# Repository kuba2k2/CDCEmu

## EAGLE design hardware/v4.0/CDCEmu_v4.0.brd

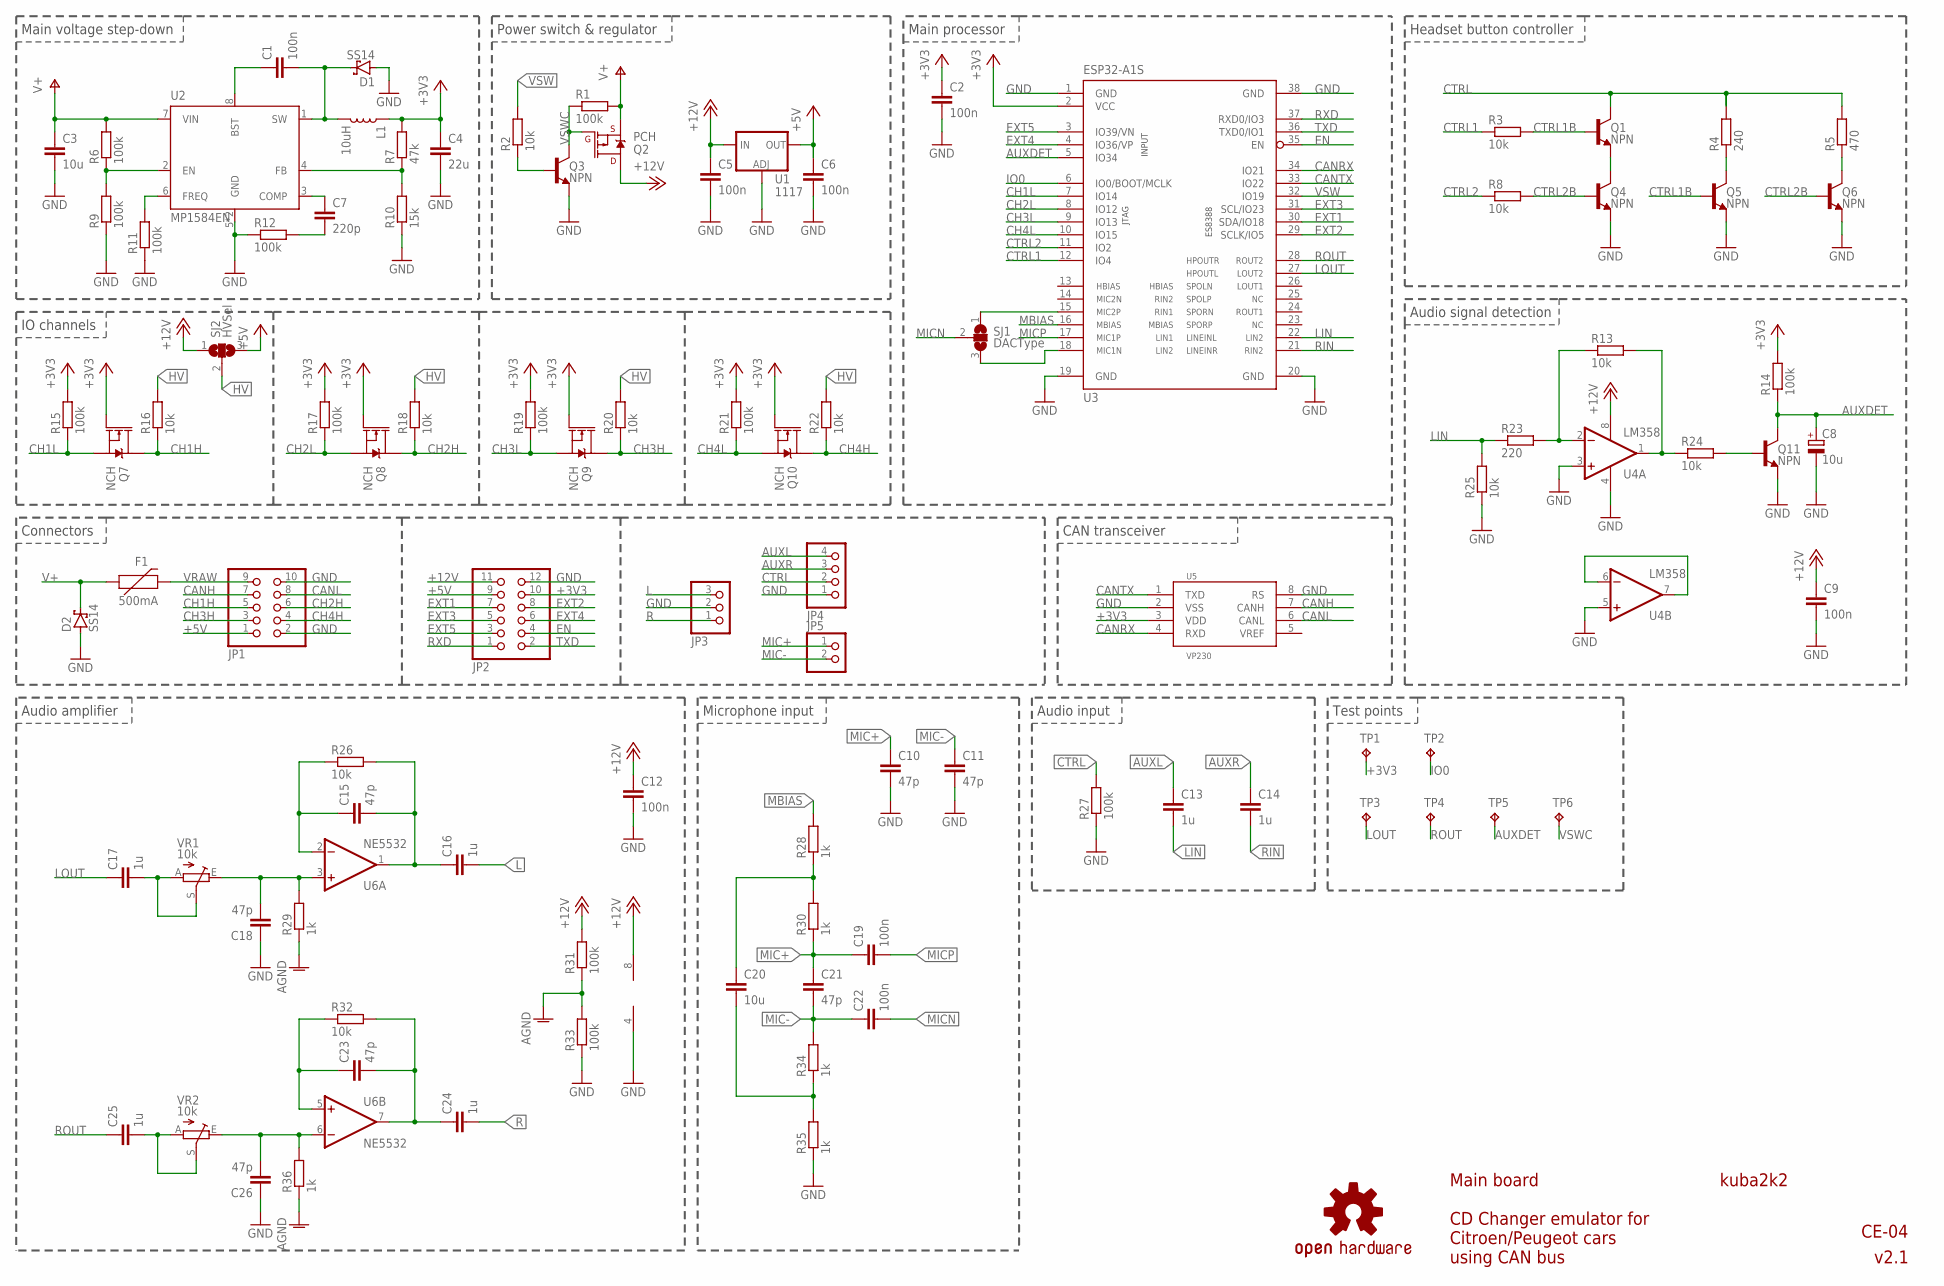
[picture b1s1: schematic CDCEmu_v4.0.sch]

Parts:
C1, C2, C5, C6, C9, C12, C19, C22: 100n; C0805
C3, C20: 10u; C1206
C4: 22u; C1206
C7: 220p; C0805
C8: 10u; C1206-POL
C10, C11, C15, C18, C21, C23, C26: 47p; C0805
C13, C14, C16, C17, C24, C25: 1u; C0805
D1, D2: SS14; DO-214AC
F1: 500mA; 0805
JP1: PINHD-2X5/90; 2X05/90
JP2: PINHD-2X6/90; 2X06/90
JP3: PINHD-1X3/90; 1X03/90
JP4: PINHD-1X4/90; 1X04/90
JP5: PINHD-1X2/90; 1X02/90
L1: 10uH; CR75
Q1, Q3, Q4, Q5, Q6, Q11: NPN; SOT23-3
Q2: PCH; SOT23-3
Q7, Q8, Q9, Q10: NCH; SOT23-3
R1, R6, R9, R11, R12, R14, R15, R17, R19, R21, R27, R31, R33: 100k; R0805
R2, R3, R8, R13, R16, R18, R20, R22, R24, R25, R26, R32: 10k; R0805
R4: 240; R0805
R5: 470; R0805
R7: 47k; R0805
R10: 15k; R0805
R23: 220; R0805
R28, R29, R30, R34, R35, R36: 1k; R0805
SJ1: DACType; SJ_2
SJ2: HVSel; SJ_2
TP1, TP2, TP3, TP4, TP5, TP6: TPB1,27; B1,27
U1: 1117; SOT223
U2: MP1584EN; SO08-PAD
U3: ESP32-A1S
U4: LM358; SO08
U5: VP230; SO08
U6: NE5532; SO08
U$1: OSHW-LOGO; OSHWLOGO_TOP_0.2_OUTLINE
VR1, VR2: 10k; CA6V

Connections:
+3V3: C2.1, C4.1, JP2.10, L1.P$1 (1), Q7.1 (G), Q8.1 (G), Q9.1 (G), Q10.1 (G), R7.2, R14.2, R15.2, R17.2, R19.2, R21.2, TP1.TP, U3.2 (VCC), U5.3 (VDD)
+5V: C6.1, JP1.1, JP2.9, SJ2.3, U1.2 (OUT), U1.4 (OUT)
+12V: C5.1, C9.1, C12.1, JP2.11, Q2.3 (D), R31.2, SJ2.1, U1.3 (IN), U4.8 (V+), U6.8 (V+)
AGND: R29.1, R31.1, R33.2, R36.1
AUXDET: C8.1 (+), Q11.3 (C), R14.1, TP5.TP, U3.5 (IO34)
AUXL: C13.1, JP4.4
AUXR: C14.1, JP4.3
BST: C1.1, U2.8 (BST)
CANH: JP1.7, U5.7 (CANH)
CANL: JP1.8, U5.6 (CANL)
CANRX: U3.34 (IO21), U5.4 (RXD)
CANTX: U3.33 (IO22), U5.1 (TXD)
CCE: Q1.2 (E), Q4.3 (C)
CH1H: JP1.5, Q7.3 (D), R16.1
CH1L: Q7.2 (S), R15.1, U3.7 (IO14)
CH2H: JP1.6, Q8.3 (D), R18.1
CH2L: Q8.2 (S), R17.1, U3.8 (IO12)
CH3H: JP1.3, Q9.3 (D), R20.1
CH3L: Q9.2 (S), R19.1, U3.9 (IO13)
CH4H: JP1.4, Q10.3 (D), R22.1
CH4L: Q10.2 (S), R21.1, U3.10 (IO15)
COMP: C7.1, U2.3 (COMP)
COMPD: C7.2, R12.2
CTRL: JP4.2, Q1.3 (C), R4.2, R5.2, R27.2
CTRL1: R3.1, U3.12 (IO4)
CTRL1B: Q1.1 (B), Q5.1 (B), R3.2
CTRL2: R8.1, U3.11 (IO2)
CTRL2B: Q4.1 (B), Q6.1 (B), R8.2
DET-: R13.1, R23.2, U4.2 (-IN)
DETOUT: R13.2, R24.1, U4.1 (OUT)
DET_B: Q11.1 (B), R24.2
EN: JP2.4, U3.35 (EN)
EXT1: JP2.7, U3.30 (SDA/IO18)
EXT2: JP2.8, U3.29 (SCLK/IO5)
EXT3: JP2.5, U3.31 (SCL/IO23)
EXT4: JP2.6, U3.4 (IO36/VP)
EXT5: JP2.3, U3.3 (IO39/VN)
FB: R7.1, R10.2, U2.4 (FB)
FREQ: R11.2, U2.6 (FREQ)
GND: C2.2, C3.2, C4.2, C5.2, C6.2, C8.2 (-), C9.2, C10.2, C11.2, C12.2, C18.1, C26.1, D1.A, D2.A, JP1.2, JP1.10, JP2.12, JP3.2, JP4.1, Q3.2 (E), Q4.2 (E), Q5.2 (E), Q6.2 (E), Q11.2 (E), R9.1, R10.1, R11.1, R12.1, R25.1, R27.1, R33.1, R35.1, U1.1 (ADJ), U2.5 (GND), U2.PAD (GND), U3.1 (GND), U3.19 (GND), U3.20 (GND), U3.38 (GND), U4.3 (+IN), U4.4 (V-), U4.5 (+IN), U5.2 (VSS), U5.8 (RS), U6.4 (V-)
HV: R16.2, R18.2, R20.2, R22.2, SJ2.2
IO0: TP2.TP, U3.6 (IO0/BOOT/MCLK)
L: C16.2, JP3.3
LF: C17.2, VR1.A, VR1.S
LFB: C15.2, C16.1, R26.2, U6.1 (OUT)
LIN: C13.2, R23.1, R25.2, U3.22 (LINEINL/LIN2)
LNEG: C15.1, R26.1, U6.2 (-IN)
LOUT: C17.1, TP3.TP, U3.27 (HPOUTL/LOUT2)
LPOS: C18.2, R29.2, U6.3 (+IN), VR1.E
MBIAS: R28.2, U3.16 (MBIAS)
MG+: C20.1, R28.1, R30.2
MG-: C20.2, R34.1, R35.2
MIC1N: SJ1.3, U3.18 (MIC1N/LIN2)
MIC+: C10.1, C19.1, C21.1, JP5.1, R30.1
MIC-: C11.1, C21.2, C22.1, JP5.2, R34.2
MICN: C22.2, SJ1.2
MICP: C19.2, U3.17 (MIC1P/LIN1)
MPEN: R6.1, R9.2, U2.2 (EN)
Q8C: Q5.3 (C), R4.1
Q9C: Q6.3 (C), R5.1
R: C24.2, JP3.1
RF: C25.2, VR2.A, VR2.S
RFB: C23.2, C24.1, R32.2, U6.7 (OUT)
RIN: C14.2, U3.21 (LINEINR/RIN2)
RIN1: SJ1.1, U3.15 (MIC2P/RIN1)
RNEG: C23.1, R32.1, U6.5 (+IN)
ROUT: C25.1, TP4.TP, U3.28 (HPOUTR/ROUT2)
RPOS: C26.2, R36.2, U6.6 (-IN), VR2.E
RXD: JP2.1, U3.37 (RXD0/IO3)
SW: C1.2, D1.C, L1.P$2 (2), U2.1 (SW)
TXD: JP2.2, U3.36 (TXD0/IO1)
U4FB: U4.6 (-IN), U4.7 (OUT)
V+: C3.1, D2.C, F1.1, Q2.2 (S), R1.2, R6.2, U2.7 (VIN)
VRAW: F1.2, JP1.9
VSW: R2.2, U3.32 (IO19)
VSWB: Q3.1 (B), R2.1
VSWC: Q2.1 (G), Q3.3 (C), R1.1, TP6.TP

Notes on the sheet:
Audio amplifier
Power switch & regulator
Headset button controller
Microphone input
kuba2k2
v2.1
CE-04
CD Changer emulator for Citroen/Peugeot cars using CAN bus
Main board
Audio signal detection
IO channels
Main voltage step-down
Main processor
Connectors
CAN transceiver
Audio input
Test points

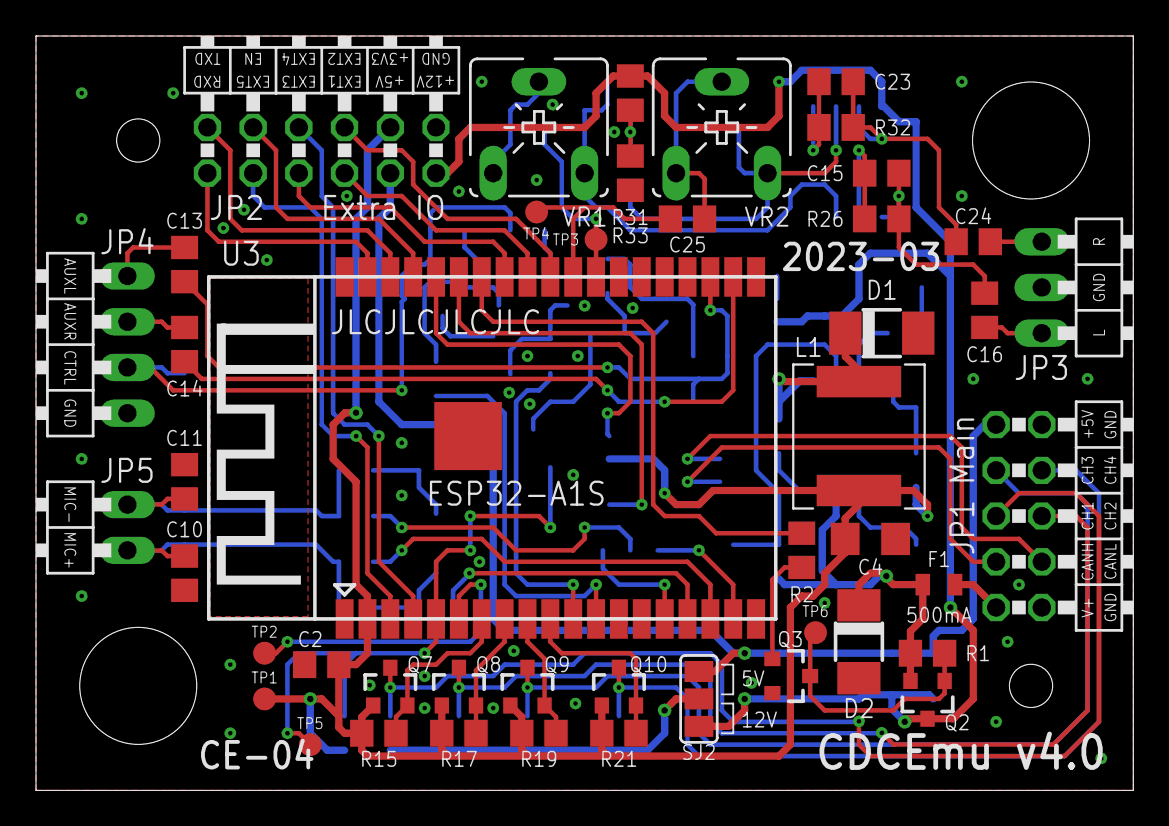
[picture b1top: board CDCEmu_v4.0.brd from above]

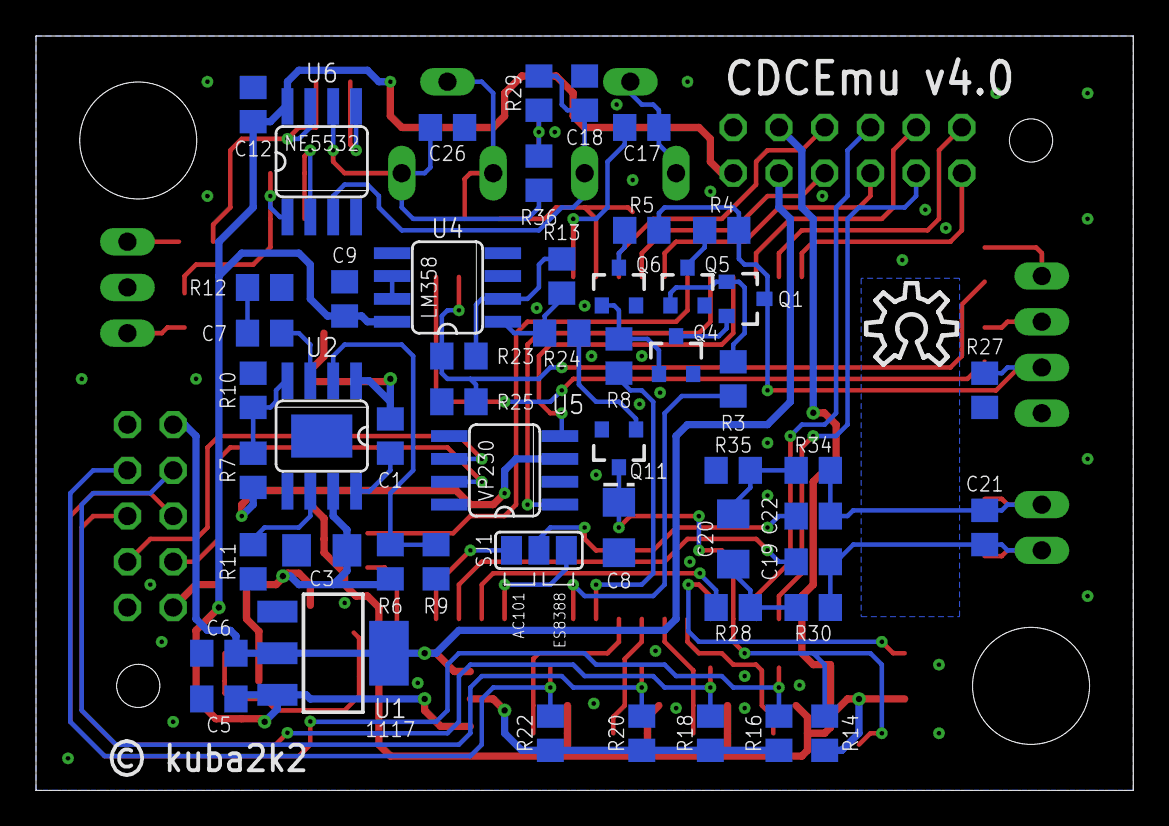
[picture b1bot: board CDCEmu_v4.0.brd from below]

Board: 2 copper layers, 61.0 x 41.9 mm, 99 parts (53 on the bottom side), 77 nets.

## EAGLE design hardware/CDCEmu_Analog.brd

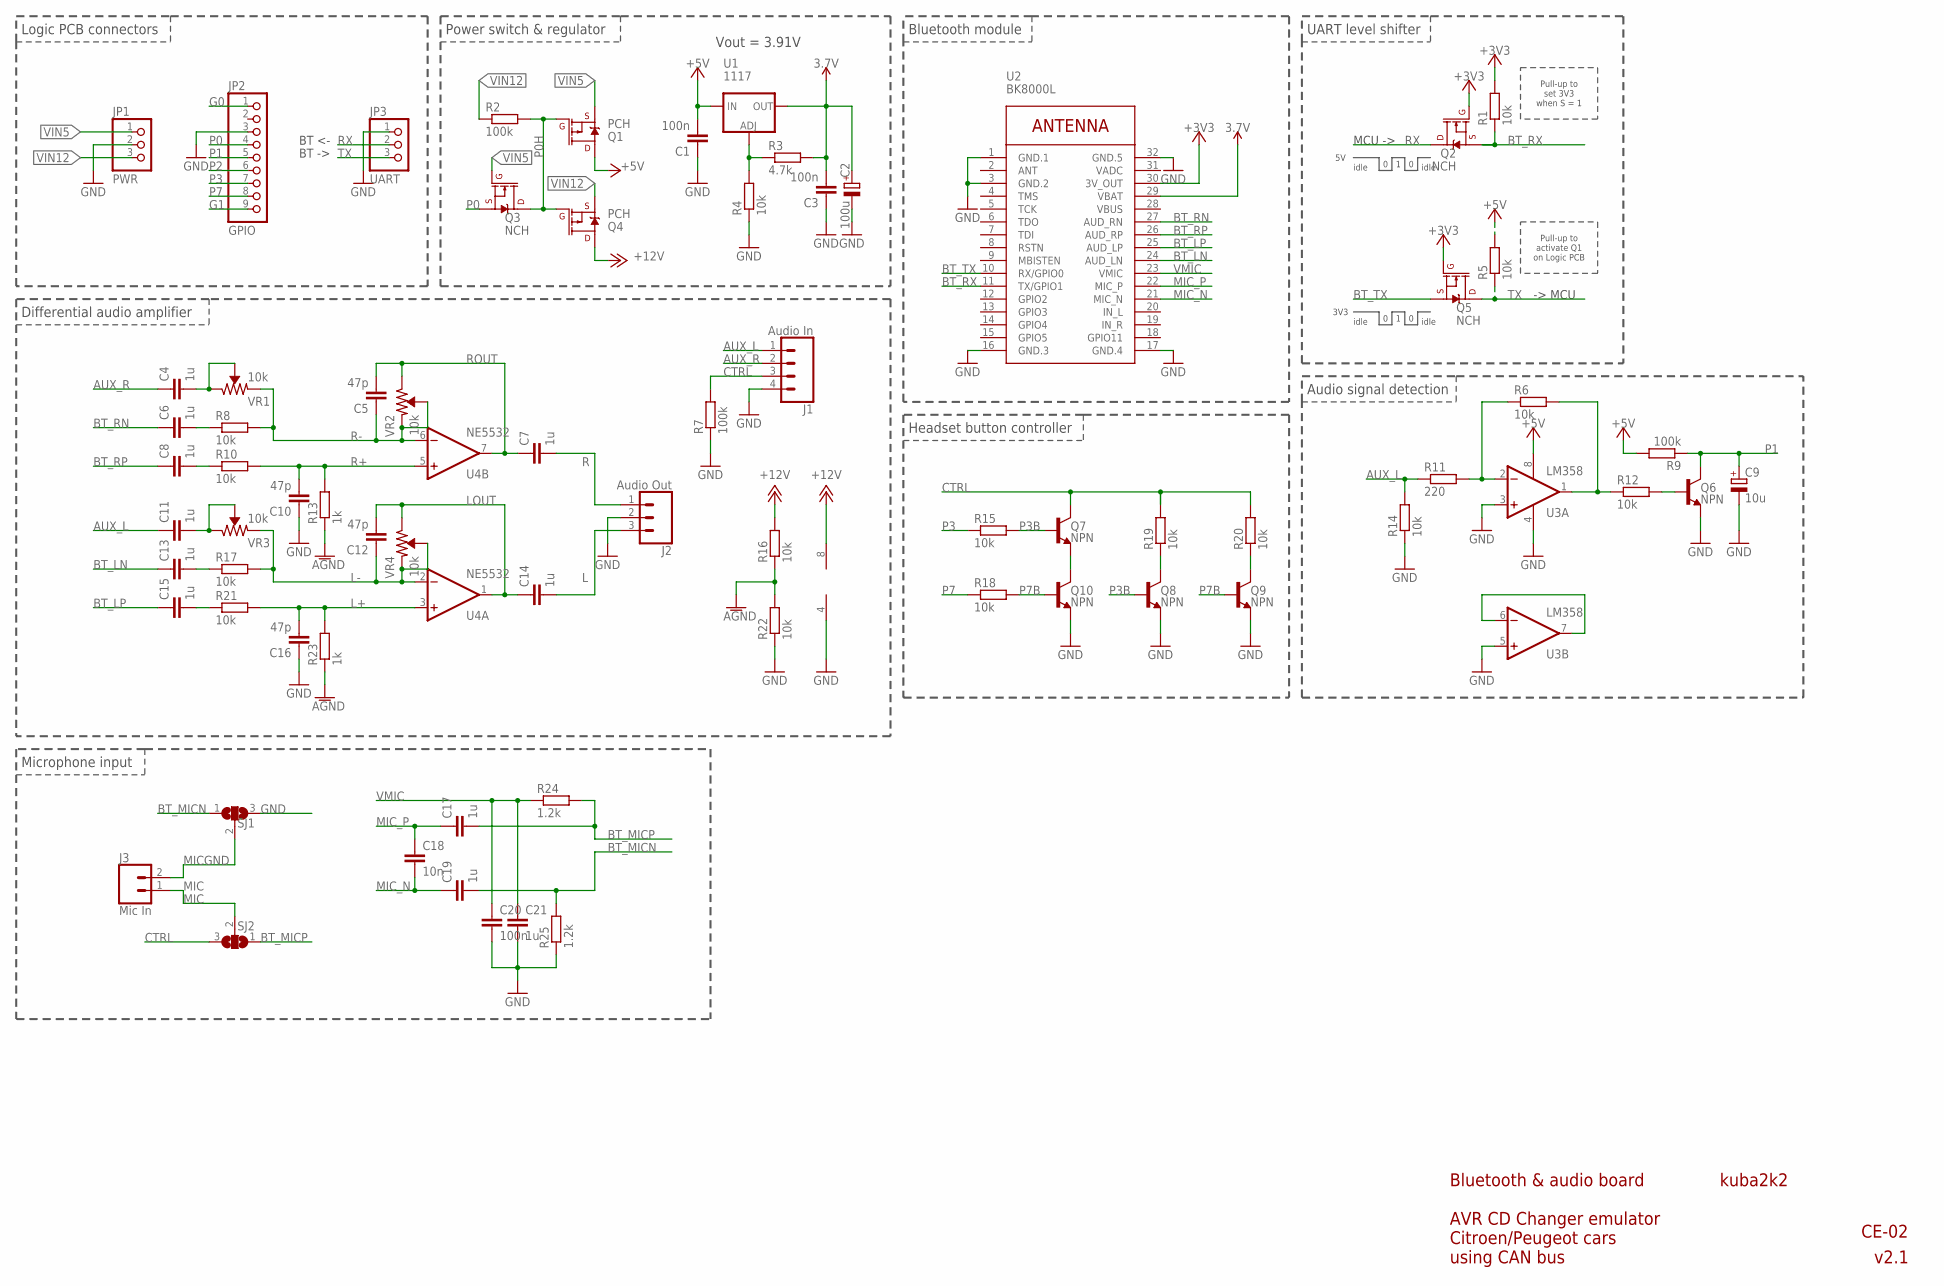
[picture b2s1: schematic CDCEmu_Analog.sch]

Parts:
C1, C3, C20: 100n; C0805
C2: 100u; SMC_B
C4, C6, C7, C8, C11, C13, C14, C15, C17, C19, C21: 1u; C0805
C5, C10, C12, C16: 47p; C0805
C9: 10u; C1206-POL
C18: 10n; C0805
J1: Audio In; JST-4-PTH
J2: Audio Out; JST-3-PTH
J3: Mic In; JST-2-PTH
JP1: PWR; 1X03
JP2: GPIO; 1X09
JP3: UART; 1X03
Q1, Q4: PCH; SOT23-3
Q2, Q3, Q5: NCH; SOT23-3
Q6, Q7, Q8, Q9, Q10: NPN; SOT23-3
R1, R4, R5, R6, R8, R10, R12, R14, R15, R16, R17, R18, R19, R20, R21, R22: 10k; R0805
R2, R7, R9: 100k; R0805
R3: 4.7k; R0805
R11: 220; R0805
R13, R23: 1k; R0805
R24, R25: 1.2k; R0805
SJ1, SJ2: SJ2W; SJ_2
U1: 1117; SOT223
U2: BK8000L; WIRELESS-BLUETOOTH-BK8000
U3: LM358; SO08
U4: NE5532; SO08
VR1, VR2, VR3, VR4: 10k; TRIMPOT-SMD-TC33X

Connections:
3.7V: C2.+, C3.2, R3.2, U1.2 (OUT), U1.4 (OUT), U2.29 (VBAT)
+3V3: Q2.1 (G), Q5.1 (G), R1.2, U2.30 (3V_OUT)
+5V: C1.2, Q1.3 (D), R5.2, R9.2, U1.3 (IN), U3.8 (V+)
+12V: Q4.3 (D), R16.2, U4.8 (V+)
ADJ: R3.1, R4.2, U1.1 (ADJ)
AGND: R13.1, R16.1, R22.2, R23.1
AUX_L: C11.1, J1.1, R11.1, R14.2
AUX_R: C4.1, J1.2
BT_LN: C13.1, U2.24 (AUD_LN)
BT_LP: C15.1, U2.25 (AUD_LP)
BT_MICN: C19.2, R25.2, SJ1.1
BT_MICP: C17.2, R24.2, SJ2.1
BT_RN: C6.1, U2.27 (AUD_RN)
BT_RP: C8.1, U2.26 (AUD_RP)
BT_RX: Q2.2 (S), R1.1, U2.11 (TX/GPIO1)
BT_TX: Q5.2 (S), U2.10 (RX/GPIO0)
CCE: Q7.2 (E), Q10.3 (C)
CTRL: J1.3, Q7.3 (C), R7.2, R19.2, R20.2, SJ2.3
DET-: R6.1, R11.2, U3.2 (-IN)
DETOUT: R6.2, R12.1, U3.1 (OUT)
DET_B: Q6.1 (B), R12.2
G0: JP2.1
G1: JP2.9
GND: C1.1, C2.-, C3.1, C9.2 (-), C10.1, C16.1, C20.2, C21.2, J1.4, J2.2, JP1.2, JP2.3, JP3.1, Q6.2 (E), Q8.2 (E), Q9.2 (E), Q10.2 (E), R4.1, R7.1, R14.1, R22.1, R25.1, SJ1.3, U2.1 (GND.1), U2.3 (GND.2), U2.16 (GND.3), U2.17 (GND.4), U2.32 (GND.5), U3.3 (+IN), U3.4 (V-), U3.5 (+IN), U4.4 (V-)
L: C14.2, J2.3
L1: C11.2, VR3.1 (CW), VR3.2 (WIPER)
L2: C13.2, R17.1
L3: C15.2, R21.1
L+: C16.2, R21.2, R23.2, U4.3 (+IN)
L-: C12.1, R17.2, U4.2 (-IN), VR3.3 (CCW), VR4.2 (WIPER), VR4.3 (CCW)
LOUT: C12.2, C14.1, U4.1 (OUT), VR4.1 (CW)
MIC: J3.1, SJ2.2
MICGND: J3.2, SJ1.2
MIC_N: C18.2, C19.1, U2.21 (MIC_N)
MIC_P: C17.1, C18.1, U2.22 (MIC_P)
P0: JP2.4, Q3.2 (S)
P0H: Q1.1 (G), Q3.3 (D), Q4.1 (G), R2.2
P1: C9.1 (+), JP2.5, Q6.3 (C), R9.1
P2: JP2.6
P3: JP2.7, R15.1
P3B: Q7.1 (B), Q8.1 (B), R15.2
P7: JP2.8, R18.1
P7B: Q9.1 (B), Q10.1 (B), R18.2
Q8C: Q8.3 (C), R19.1
Q9C: Q9.3 (C), R20.1
R: C7.2, J2.1
R1: C4.2, VR1.1 (CW), VR1.2 (WIPER)
R2: C6.2, R8.1
R3: C8.2, R10.1
R+: C10.2, R10.2, R13.2, U4.5 (+IN)
R-: C5.1, R8.2, U4.6 (-IN), VR1.3 (CCW), VR2.2 (WIPER), VR2.3 (CCW)
ROUT: C5.2, C7.1, U4.7 (OUT), VR2.1 (CW)
RX: JP3.2, Q2.3 (D)
TX: JP3.3, Q5.3 (D), R5.1
U4FB: U3.6 (-IN), U3.7 (OUT)
VADC: U2.31 (VADC)
VIN5: JP1.1, Q1.2 (S), Q3.1 (G)
VIN12: JP1.3, Q4.2 (S), R2.1
VMIC: C20.1, C21.1, R24.1, U2.23 (VMIC)

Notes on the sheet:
Differential audio amplifier
Logic PCB connectors
Power switch & regulator
BT <-
BT ->
MCU ->
-> MCU
UART level shifter
Pull-up to activate Q1 on Logic PCB
idle
Pull-up to set 3V3 when S = 1
Bluetooth module
Headset button controller
Microphone input
3V3
kuba2k2
v2.1
CE-02
Vout = 3.91V
AVR CD Changer emulator Citroen/Peugeot cars using CAN bus
Bluetooth & audio board
Audio signal detection

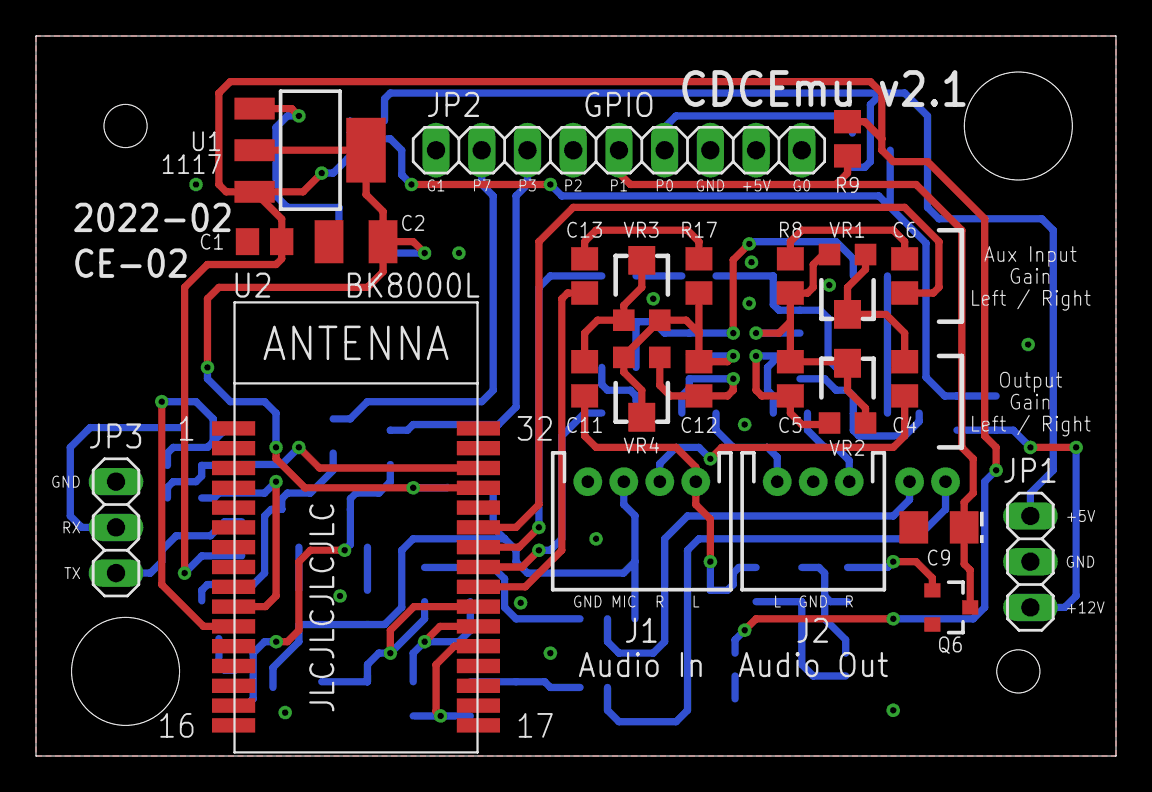
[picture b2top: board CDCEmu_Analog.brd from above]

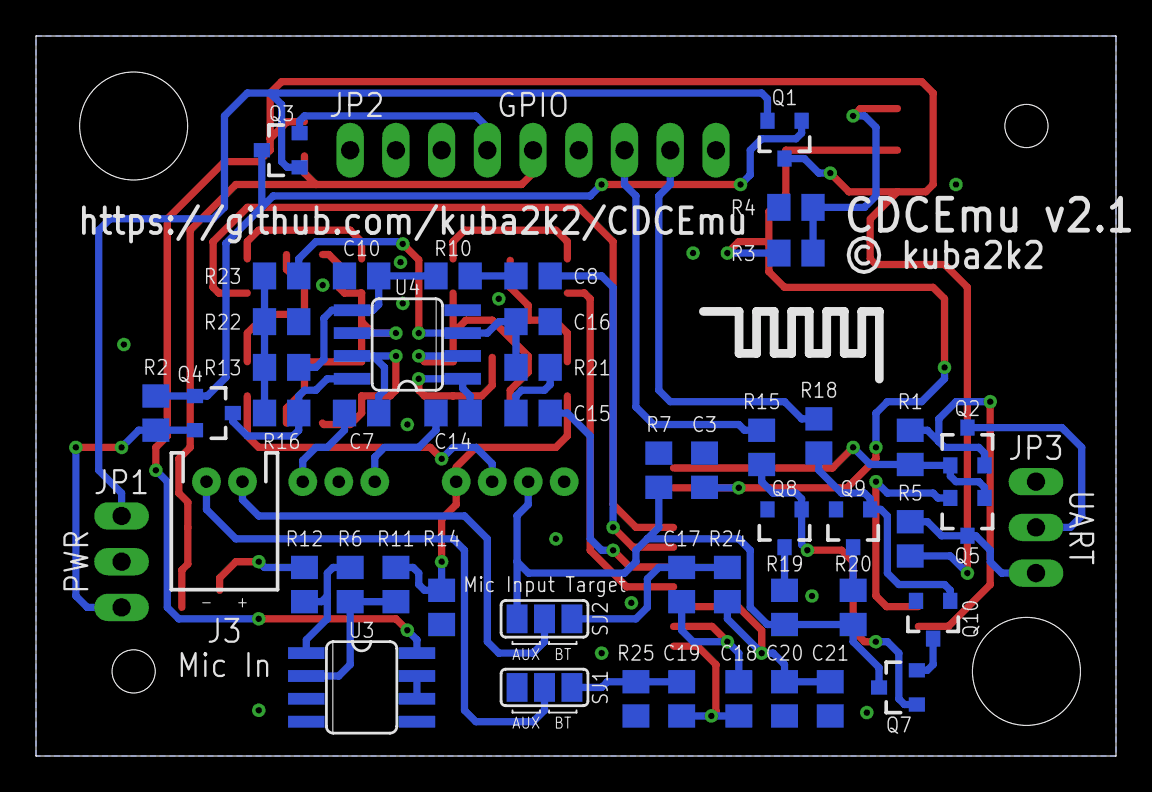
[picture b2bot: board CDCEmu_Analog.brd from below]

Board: 2 copper layers, 60.0 x 40.0 mm, 72 parts (48 on the bottom side), 55 nets.

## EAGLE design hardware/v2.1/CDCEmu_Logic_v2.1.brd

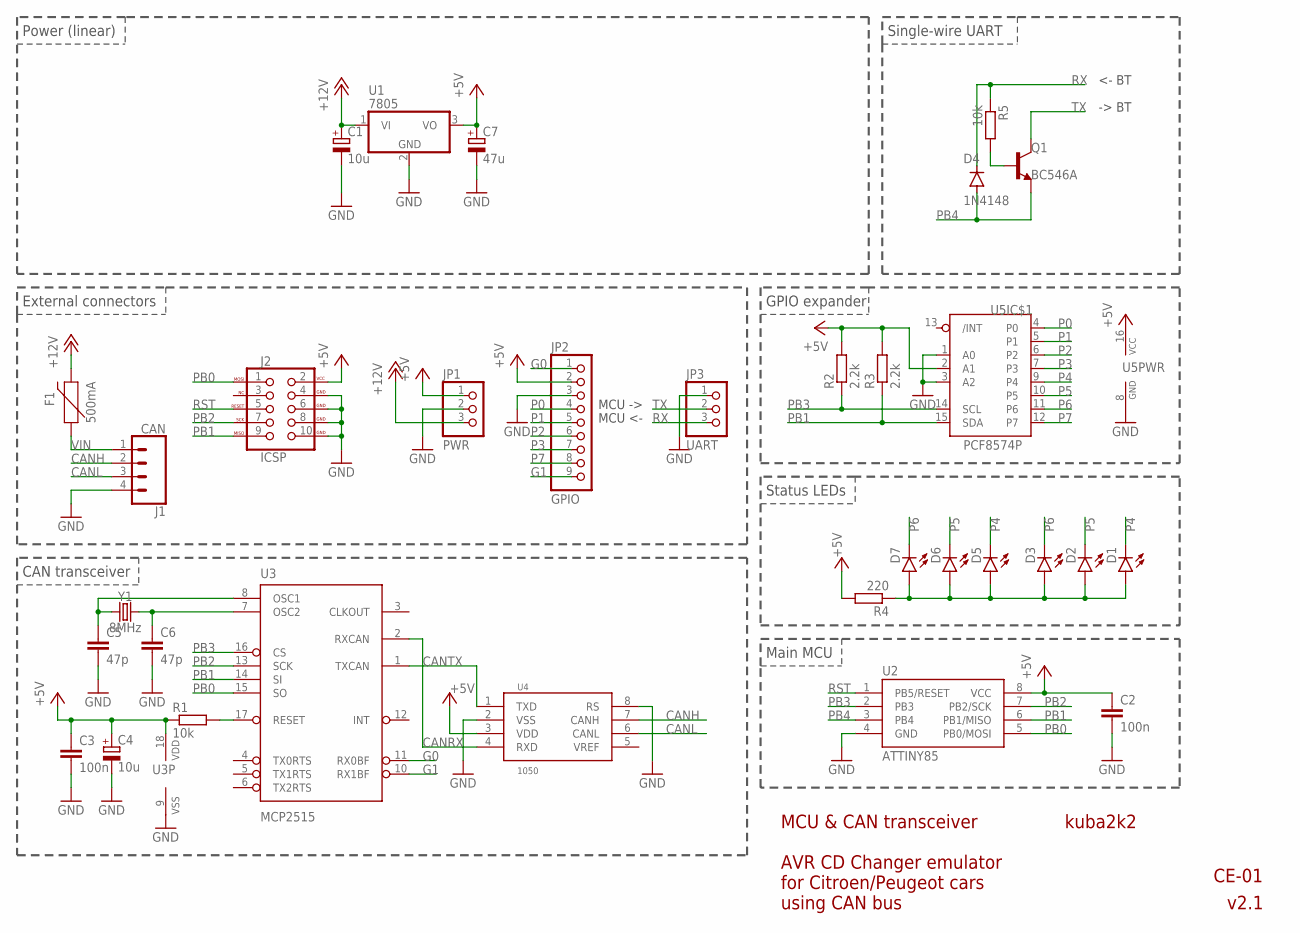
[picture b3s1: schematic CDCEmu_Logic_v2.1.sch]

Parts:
C1: 10u; C2512-POL
C2, C3: 100n; C050-024X044
C4: 10u; E2,5-6
C5, C6: 47p; C0805
C7: 47u; C2512-POL
D1, D2, D3: LED3MM
D4: 1N4148; DO35-7
D5, D6, D7: LEDCHIP-LED0805; CHIP-LED0805
F1: 500mA; 1812
J1: CAN; JST-4-PTH
J2: ICSP; 2X5-SHROUDED_LOCK
JP1: PWR; 1X03
JP2: GPIO; 1X09
JP3: UART; 1X03
Q1: BC546A; TO92-EBC
R1: 10k; R0805
R2, R3: 2.2k; R0805
R4: 220; 0204/7
R5: 10k; 0204/7
U1: 7805; TO220H-NOHOLE
U2: ATTINY85; PDIP08_300MIL
U3: MCP2515; SO18W
U4: 1050; SO08
U5: PCF8574P; DIL16
Y1: 8MHz; HC49U

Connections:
+5V: C2.1, C3.1, C4.+, C7.+, J2.2 (VCC), JP1.1, JP2.2, R1.1, R2.2, R3.2, R4.2, U1.3 (VO), U2.8 (VCC), U3.18 (VDD), U4.3 (VDD), U5.2 (A1), U5.16 (VCC)
+12V: C1.+, F1.2, JP1.3, U1.1 (VI)
CANH: J1.2, U4.7 (CANH)
CANL: J1.3, U4.6 (CANL)
CANOSC1: C5.1, U3.8 (OSC1), Y1.1
CANOSC2: C6.1, U3.7 (OSC2), Y1.2
CANRST: R1.2, U3.17 (RESET)
CANRX: U3.2 (RXCAN), U4.4 (RXD)
CANTX: U3.1 (TXCAN), U4.1 (TXD)
G0: JP2.1, U3.11 (RX0BF)
G1: JP2.9, U3.10 (RX1BF)
GND: C1.-, C2.2, C3.2, C4.-, C5.2, C6.2, C7.-, J1.4, J2.4 (GND), J2.6 (GND), J2.8 (GND), J2.10 (GND), JP1.2, JP2.3, JP3.1, U1.2 (GND), U2.4 (GND), U3.9 (VSS), U4.2 (VSS), U4.8 (RS), U5.1 (A0), U5.3 (A2), U5.8 (GND)
LED_A: D1.A, D2.A, D3.A, D5.A, D6.A, D7.A, R4.1
P0: JP2.4, U5.4 (P0)
P1: JP2.5, U5.5 (P1)
P2: JP2.6, U5.6 (P2)
P3: JP2.7, U5.7 (P3)
P4: D1.K (C), D5.C, U5.9 (P4)
P5: D2.K (C), D6.C, U5.10 (P5)
P6: D3.K (C), D7.C, U5.11 (P6)
P7: JP2.8, U5.12 (P7)
PB0: J2.1 (MOSI), U2.5 (PB0/MOSI), U3.15 (SO)
PB1: J2.9 (MISO), R3.1, U2.6 (PB1/MISO), U3.14 (SI), U5.15 (SDA)
PB2: J2.7 (SCK), U2.7 (PB2/SCK), U3.13 (SCK)
PB3: R2.1, U2.2 (PB3), U3.16 (CS), U5.14 (SCL)
PB4: D4.A, Q1.E, U2.3 (PB4)
RST: J2.5 (RESET), U2.1 (PB5/RESET)
RX: D4.C, JP3.3, R5.1
TX: JP3.2, Q1.C
TXB: Q1.B, R5.2
VIN: F1.1, J1.1

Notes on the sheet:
Power (linear)
Single-wire UART
External connectors
CAN transceiver
Main MCU
Status LEDs
GPIO expander
-> BT
<- BT
MCU ->
MCU <-
kuba2k2
v2.1
CE-01
AVR CD Changer emulator for Citroen/Peugeot cars using CAN bus
MCU & CAN transceiver

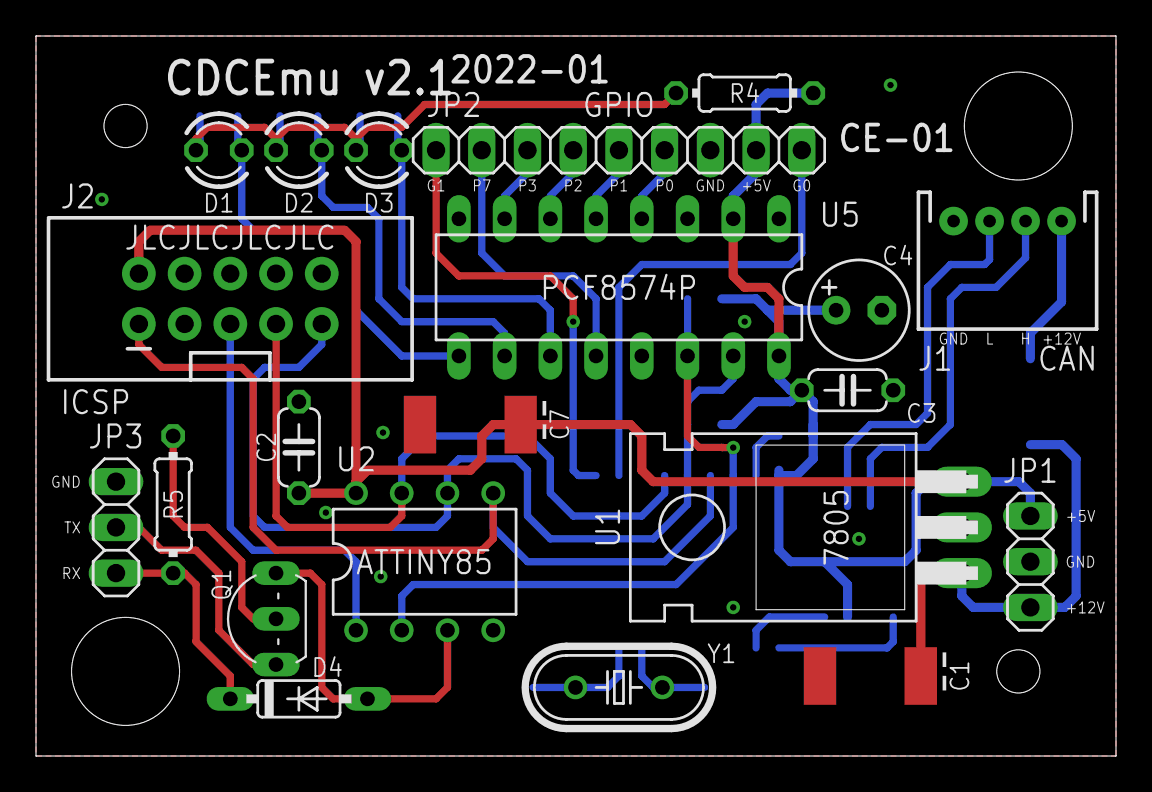
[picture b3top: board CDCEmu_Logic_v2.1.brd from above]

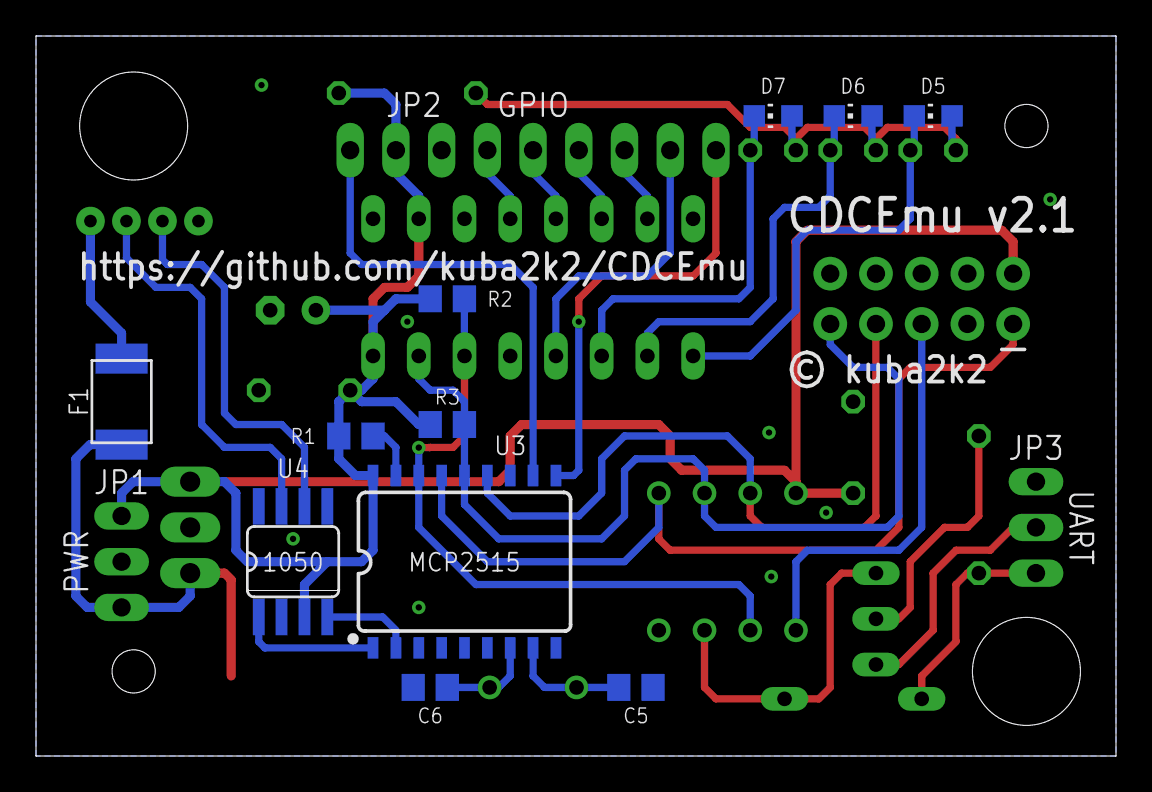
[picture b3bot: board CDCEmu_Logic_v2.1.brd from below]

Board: 2 copper layers, 60.0 x 40.0 mm, 32 parts (11 on the bottom side), 31 nets.

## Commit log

2019-07-09 Add serial open/close files
2019-07-10 Add input packets
2019-07-10 Add output packets
2019-07-18 Add main source file
2021-05-15 Add LICENSE
2021-05-15 Fix compatibility with Arduino IDE
2021-05-15 Add local MCP2515 library to support ATtiny SPI.
2021-05-15 Support Arduino and ATtiny debug logging
2021-05-19 Prepare to use with the ATTinyCore
2021-05-19 Remove avr/io.h include
2021-05-19 Implement picoUART debug logging
2021-05-20 Remove code
2021-05-20 Add Makefile and Visual Studio Code configuration
2021-05-20 Add i2c library
2021-05-20 Add pcf8574 library
2021-05-20 Add uart library
2021-05-23 Add spi library
2021-05-23 Add mcp2515 library
2021-05-23 Add CAN message sending
2021-05-23 Add CAN message receiving
2021-05-24 Implement delay timers
2021-05-25 Implement draft CDC packet receiving and sending
2021-05-26 Optimize packet sending code
2021-05-26 Add packet definition macros
2021-05-28 Move global timers to Timer1
2021-05-28 Replace picoUART with the AVR274 Single-wire Software UART
2021-05-30 Rename UART-related methods
2021-05-30 Remove stdio UART debug methods
2021-05-30 Implement UART RX buffer
2021-05-31 Rename uart_available to readable
2021-05-31 Implement UART TX buffer
2021-05-31 Remove unused UART flag defines
2021-05-31 Implement UART string receiving and pgmspace transmitting
2021-05-31 Add UART RX buffer flushing
2021-05-31 Add sample AT command support
2021-05-31 Move static packet data to PROGMEM
2021-06-23 Refactor code into separate units
2021-06-24 Implement packets 0x0E2 and 0x531
2021-06-24 Add conditional IO (re)initializing
2021-06-24 Fix packet timers skipping issue
2021-06-24 Allow using up to 16 timers and data bytes
2021-06-24 Add status LEDs
2021-06-24 Implement BSI Ignition packet
2021-06-25 Implement vehicle sleep mode (BSI Ignition OFF)
2021-06-25 Improve sleep mode behavior during bus activity
2021-06-25 Add more debugging
2021-06-25 Fix sleep mode, again
2022-03-07 Add hardware design files
2022-03-07 Release hardware v2.0
2022-03-07 [HW] Refactor logic PCB
2022-03-07 [HW] Add audio PCB design files
2022-03-07 [HW] Add Logic PCB AP5100 step-down variant (unfinished, deprecated)
2022-03-08 [HW] Add audio gain control trimpots
2022-03-10 [HW/Logic] Add pinout labels to connectors
2022-03-10 [HW/Analog] Add audio signal detection
2022-03-10 [HW/Analog] Separate Q8 and Q9
2022-03-10 [HW/Logic] Change preview soldermask color, move texts
2022-03-11 [HW] Release v2.1
2022-04-11 [FW] Add CMake build
2022-04-11 [FW] Refactor code a bit
2022-04-11 [FW] Reformat code with clang-format
2022-04-11 [FW] Use #pragma once
2022-04-11 [FW] Add project .clang-format
2022-04-13 [FW] Add UART debug macros
2022-04-15 [FW] Remove Makefiles
2022-04-15 [FW] Add initial support for Analog PCB
2022-04-15 [FW] Migrate to Kconfig
2022-04-15 [FW] Move code to src directory
2022-04-15 [FW] Reformat code
2022-04-15 [FW] Add base Bluetooth code
2022-04-16 [FW] Implement Bluetooth support
2022-04-18 [FW] Implement AUX input support
2022-07-08 [HW/Analog] Fix swapped Bluetooth RX and TX
2022-07-08 [HW/Analog] Correct Vol+/- control transistors
2023-04-02 [HW] Release v4.0
2023-04-24 [HW] Correct resistor values
2023-04-24 [HW] Update .gitignore

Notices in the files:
hardware/CDCEmu_Analog.brd:
© kuba2k2
parts and their libraries:
diy-modules: Released under the Creative Commons Attribution 4.0 International License: http://creativecommons.org/licenses/by/4.0
SparkFun-Connectors: Licensing: Creative Commons ShareAlike 4.0 International - https://creativecommons.org/licenses/by-sa/4.0
